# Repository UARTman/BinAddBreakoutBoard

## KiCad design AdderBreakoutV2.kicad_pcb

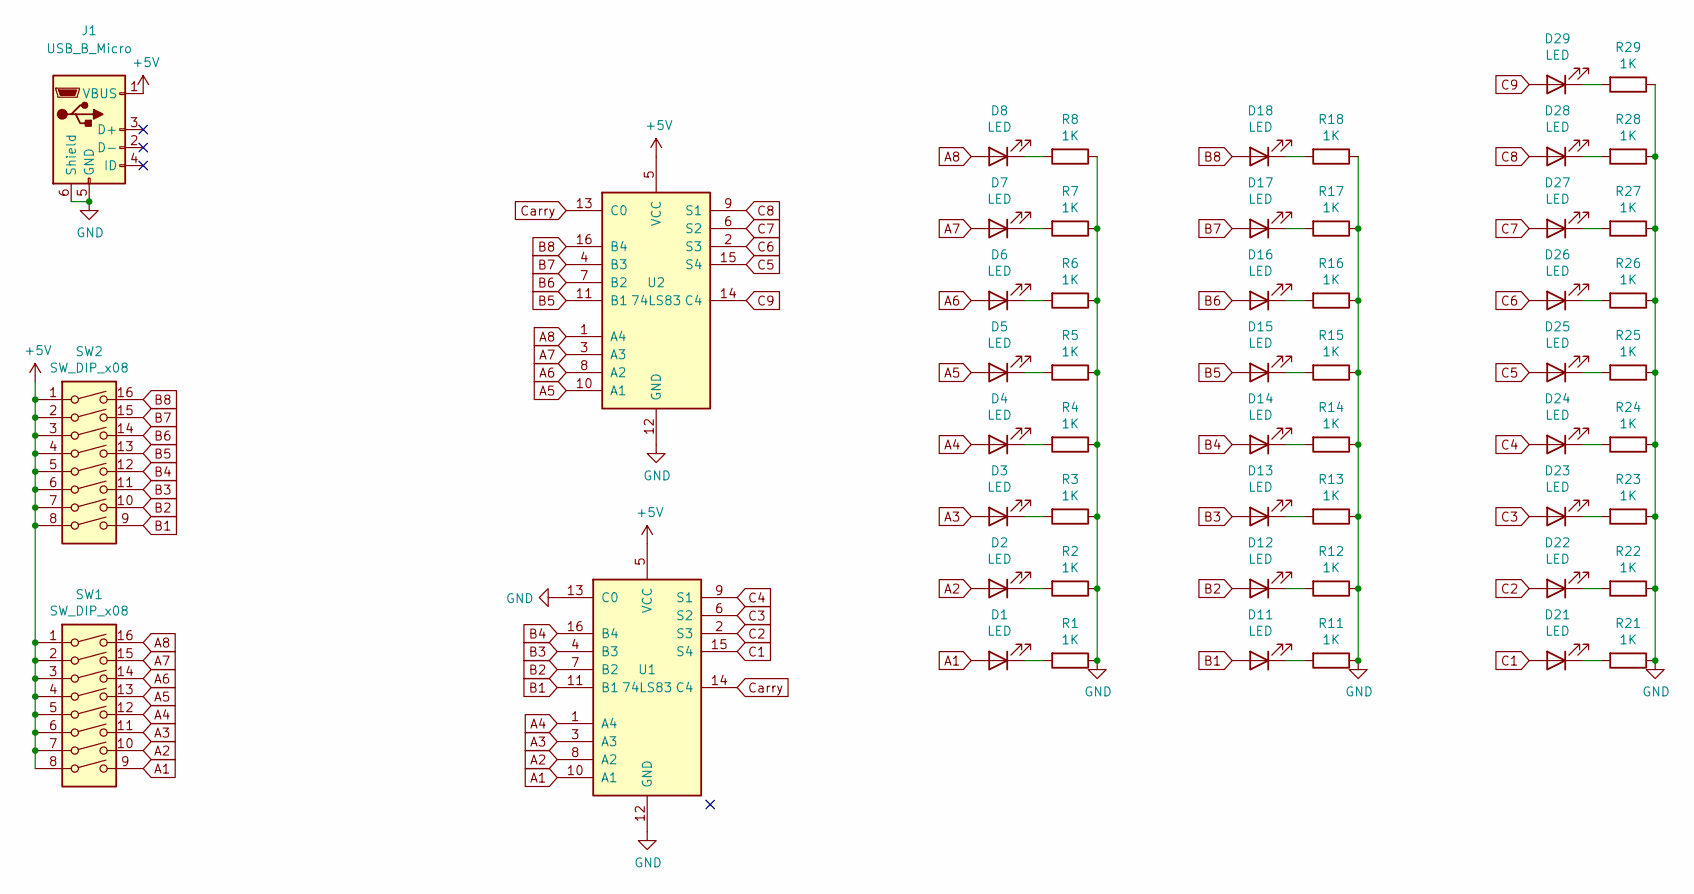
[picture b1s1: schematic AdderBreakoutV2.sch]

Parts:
D1, D2, D3, D4, D5, D6, D7, D8, D11, D12, D13, D14, D15, D16, D17, D18, D21, D22, D23, D24, D25, D26, D27, D28, D29: LED; LED_D3.0mm
J1: USB_B_Micro; USB_B_Lumberg_2411_02_Horizontal
R1, R2, R3, R4, R5, R6, R7, R8, R11, R12, R13, R14, R15, R16, R17, R18, R21, R22, R23, R24, R25, R26, R27, R28, R29: 1K; R_Axial_DIN0414_L11.9mm_D4.5mm_P15.24mm_Horizontal
SW1, SW2: SW_DIP_x08; DIP-16_W7.62mm
U1, U2: 74LS83; DIP-16_W7.62mm_Socket

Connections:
+5V: J1.1 (VBUS), SW1.1, SW1.2, SW1.3, SW1.4, SW1.5, SW1.6, SW1.7, SW1.8, SW2.1, SW2.2, SW2.3, SW2.4, SW2.5, SW2.6, SW2.7, SW2.8, U1.5 (VCC), U2.5 (VCC)
A1: D1.2 (A), SW1.9, U1.10 (A1)
A2: D2.2 (A), SW1.10, U1.8 (A2)
A3: D3.2 (A), SW1.11, U1.3 (A3)
A4: D4.2 (A), SW1.12, U1.1 (A4)
A5: D5.2 (A), SW1.13, U2.10 (A1)
A6: D6.2 (A), SW1.14, U2.8 (A2)
A7: D7.2 (A), SW1.15, U2.3 (A3)
A8: D8.2 (A), SW1.16, U2.1 (A4)
B1: D11.2 (A), SW2.9, U1.11 (B1)
B2: D12.2 (A), SW2.10, U1.7 (B2)
B3: D13.2 (A), SW2.11, U1.4 (B3)
B4: D14.2 (A), SW2.12, U1.16 (B4)
B5: D15.2 (A), SW2.13, U2.11 (B1)
B6: D16.2 (A), SW2.14, U2.7 (B2)
B7: D17.2 (A), SW2.15, U2.4 (B3)
B8: D18.2 (A), SW2.16, U2.16 (B4)
C1: D21.2 (A), U1.15 (S4)
C2: D22.2 (A), U1.2 (S3)
C3: D23.2 (A), U1.6 (S2)
C4: D24.2 (A), U1.9 (S1)
C5: D25.2 (A), U2.15 (S4)
C6: D26.2 (A), U2.2 (S3)
C7: D27.2 (A), U2.6 (S2)
C8: D28.2 (A), U2.9 (S1)
C9: D29.2 (A), U2.14 (C4)
Carry: U1.14 (C4), U2.13 (C0)
GND: J1.5 (GND), J1.6 (Shield), R1.1, R2.1, R3.1, R4.1, R5.1, R6.1, R7.1, R8.1, R11.1, R12.1, R13.1, R14.1, R15.1, R16.1, R17.1, R18.1, R21.1, R22.1, R23.1, R24.1, R25.1, R26.1, R27.1, R28.1, R29.1, U1.12 (GND), U1.13 (C0), U2.12 (GND)
unnamed: D1.1 (K), R1.2
unnamed: D2.1 (K), R2.2
unnamed: D3.1 (K), R3.2
unnamed: D4.1 (K), R4.2
unnamed: D5.1 (K), R5.2
unnamed: D6.1 (K), R6.2
unnamed: D7.1 (K), R7.2
unnamed: D8.1 (K), R8.2
unnamed: D11.1 (K), R11.2
unnamed: D12.1 (K), R12.2
unnamed: D13.1 (K), R13.2
unnamed: D14.1 (K), R14.2
unnamed: D15.1 (K), R15.2
unnamed: D16.1 (K), R16.2
unnamed: D17.1 (K), R17.2
unnamed: D18.1 (K), R18.2
unnamed: D21.1 (K), R21.2
unnamed: D22.1 (K), R22.2
unnamed: D23.1 (K), R23.2
unnamed: D24.1 (K), R24.2
unnamed: D25.1 (K), R25.2
unnamed: D26.1 (K), R26.2
unnamed: D27.1 (K), R27.2
unnamed: D28.1 (K), R28.2
unnamed: D29.1 (K), R29.2

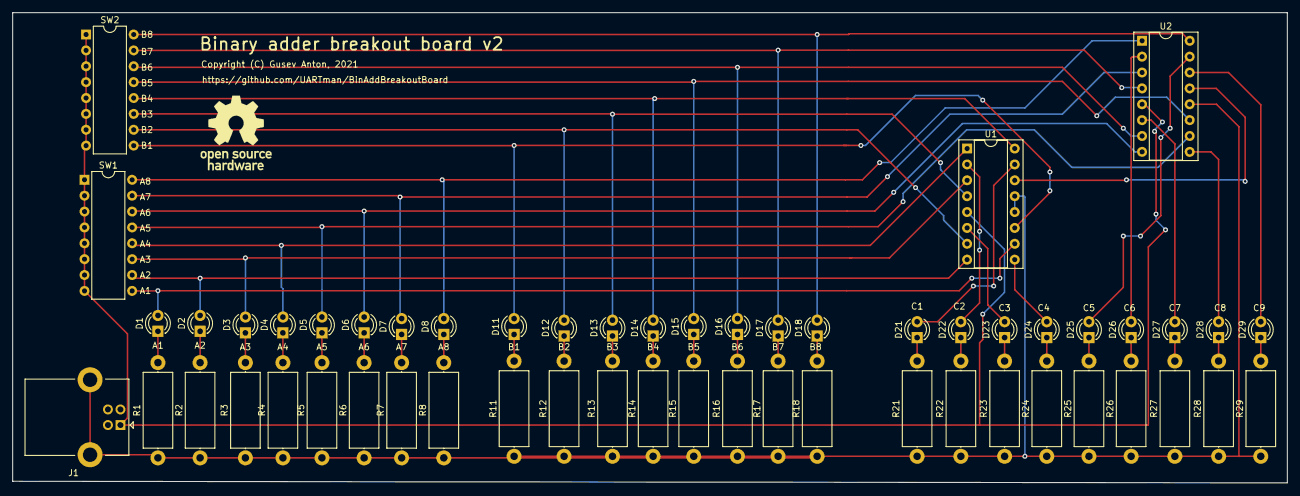
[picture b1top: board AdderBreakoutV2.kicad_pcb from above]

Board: 2 copper layers, 204.0 x 75.2 mm, 55 parts (0 on the bottom side), 53 nets.

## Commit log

2021-06-05 Init
2021-06-05 Add measurements

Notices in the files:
AdderBreakoutV2.kicad_pcb:
Copyright (C) Gusev Anton, 2021
